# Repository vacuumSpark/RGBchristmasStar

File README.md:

# RGBchristmasStar
Custom PCB for having addressable RGB LEDs driven by an ESP12 (ESP8266) with WLED firmware in a star shaped Christmas ornament normally meant for a tea light

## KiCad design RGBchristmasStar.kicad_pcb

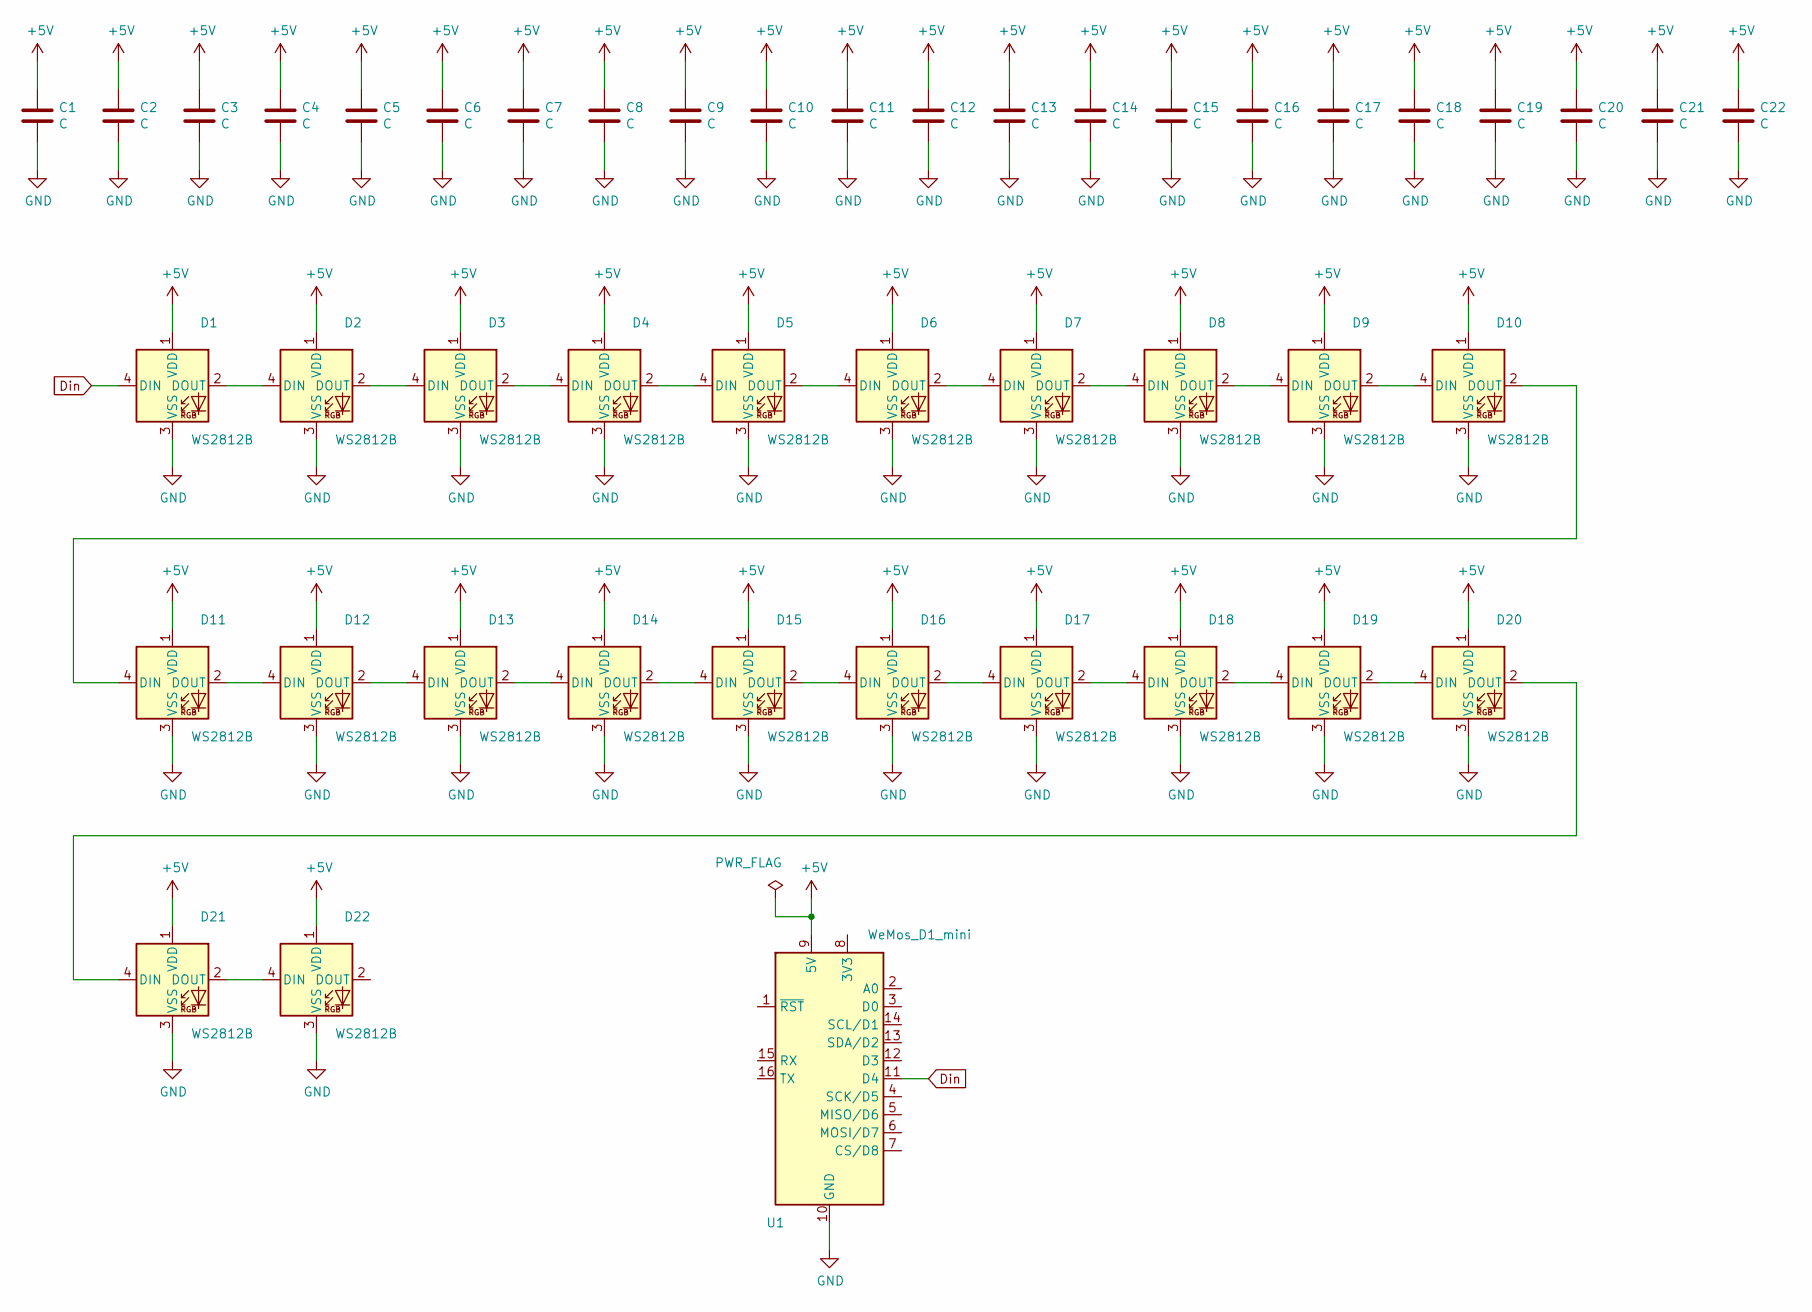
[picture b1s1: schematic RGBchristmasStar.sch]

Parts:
C1, C2, C3, C4, C5, C6, C7, C8, C9, C10, C11, C12, C13, C14, C15, C16, C17, C18, C19, C20, C21, C22: C; C_0805_2012Metric; JLCPCB Part # C28233
D1, D2, D3, D4, D5, D6, D7, D8, D9, D10, D11, D12, D13, D14, D15, D16, D17, D18, D19, D20, D21, D22: WS2812B; WS2812B-Mini; JLCPCB Part # C114583
U1: WeMos_D1_mini; WEMOS_D1_mini_light_SMD_header

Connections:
+5V: C1.1, C2.1, C3.1, C4.1, C5.1, C6.1, C7.1, C8.1, C9.1, C10.1, C11.1, C12.1, C13.1, C14.1, C15.1, C16.1, C17.1, C18.1, C19.1, C20.1, C21.1, C22.1, D1.1 (VDD), D2.1 (VDD), D3.1 (VDD), D4.1 (VDD), D5.1 (VDD), D6.1 (VDD), D7.1 (VDD), D8.1 (VDD), D9.1 (VDD), D10.1 (VDD), D11.1 (VDD), D12.1 (VDD), D13.1 (VDD), D14.1 (VDD), D15.1 (VDD), D16.1 (VDD), D17.1 (VDD), D18.1 (VDD), D19.1 (VDD), D20.1 (VDD), D21.1 (VDD), D22.1 (VDD), U1.9 (5V)
Din: D1.4 (DIN), U1.11 (D4)
GND: C1.2, C2.2, C3.2, C4.2, C5.2, C6.2, C7.2, C8.2, C9.2, C10.2, C11.2, C12.2, C13.2, C14.2, C15.2, C16.2, C17.2, C18.2, C19.2, C20.2, C21.2, C22.2, D1.3 (VSS), D2.3 (VSS), D3.3 (VSS), D4.3 (VSS), D5.3 (VSS), D6.3 (VSS), D7.3 (VSS), D8.3 (VSS), D9.3 (VSS), D10.3 (VSS), D11.3 (VSS), D12.3 (VSS), D13.3 (VSS), D14.3 (VSS), D15.3 (VSS), D16.3 (VSS), D17.3 (VSS), D18.3 (VSS), D19.3 (VSS), D20.3 (VSS), D21.3 (VSS), D22.3 (VSS), U1.10 (GND)
unnamed: D1.2 (DOUT), D2.4 (DIN)
unnamed: D2.2 (DOUT), D3.4 (DIN)
unnamed: D3.2 (DOUT), D4.4 (DIN)
unnamed: D4.2 (DOUT), D5.4 (DIN)
unnamed: D5.2 (DOUT), D6.4 (DIN)
unnamed: D6.2 (DOUT), D7.4 (DIN)
unnamed: D7.2 (DOUT), D8.4 (DIN)
unnamed: D8.2 (DOUT), D9.4 (DIN)
unnamed: D10.2 (DOUT), D11.4 (DIN)
unnamed: D9.2 (DOUT), D10.4 (DIN)
unnamed: D11.2 (DOUT), D12.4 (DIN)
unnamed: D12.2 (DOUT), D13.4 (DIN)
unnamed: D13.2 (DOUT), D14.4 (DIN)
unnamed: D14.2 (DOUT), D15.4 (DIN)
unnamed: D15.2 (DOUT), D16.4 (DIN)
unnamed: D16.2 (DOUT), D17.4 (DIN)
unnamed: D17.2 (DOUT), D18.4 (DIN)
unnamed: D18.2 (DOUT), D19.4 (DIN)
unnamed: D19.2 (DOUT), D20.4 (DIN)
unnamed: D20.2 (DOUT), D21.4 (DIN)
unnamed: D21.2 (DOUT), D22.4 (DIN)

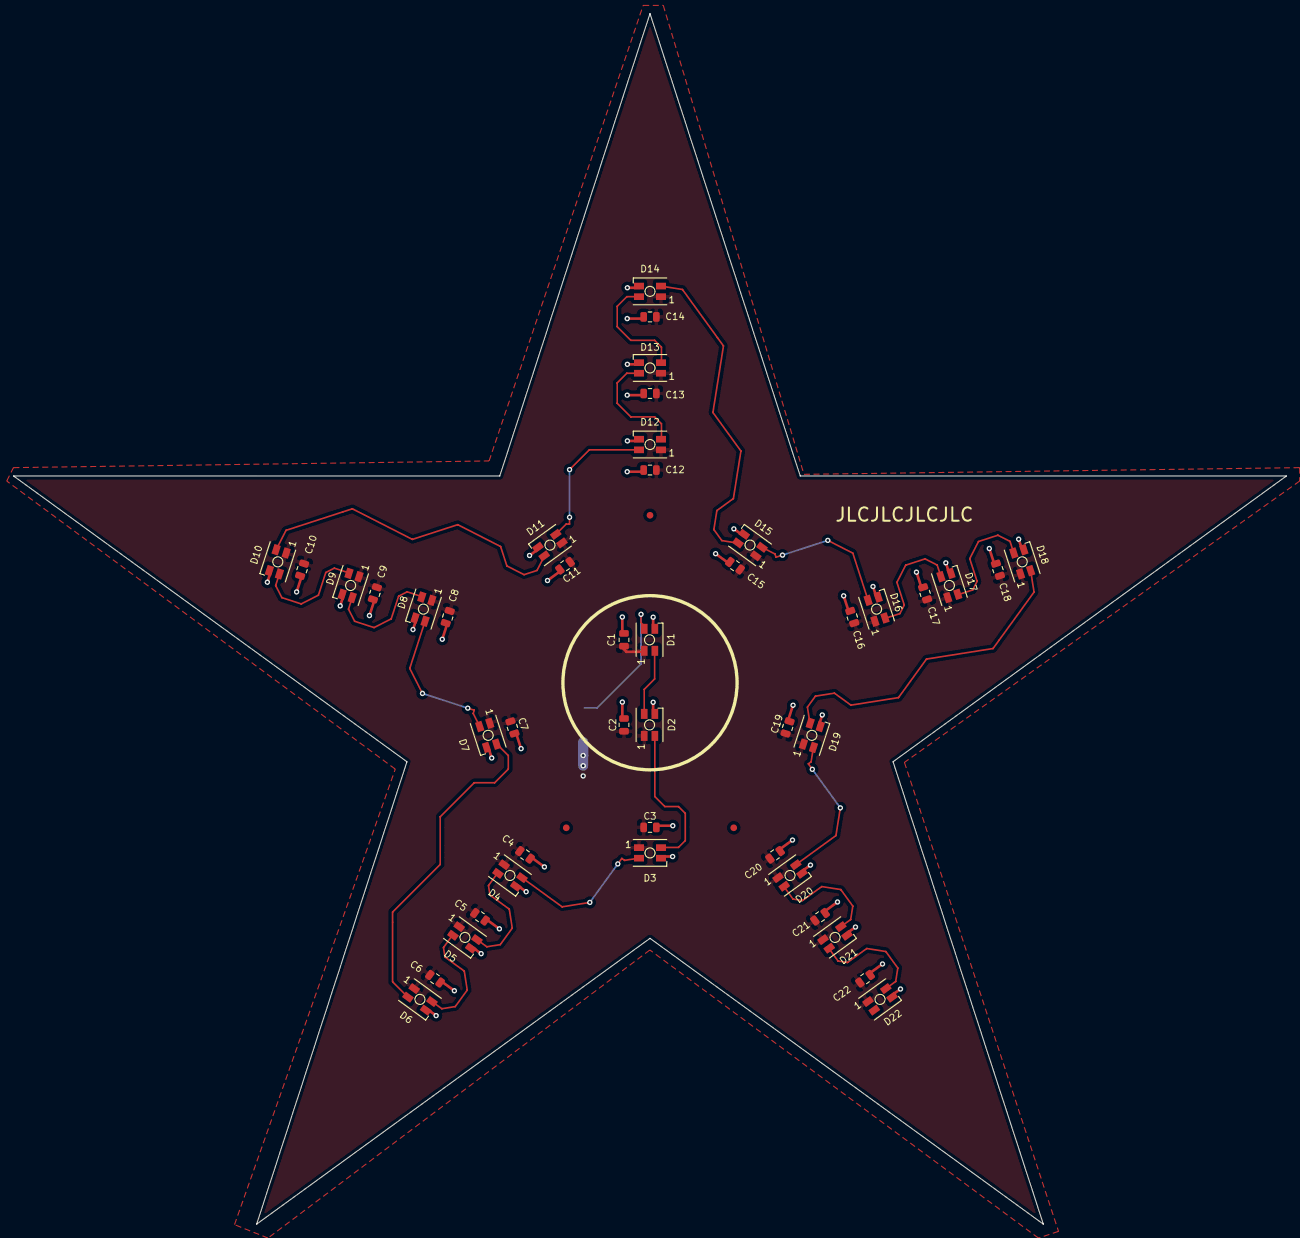
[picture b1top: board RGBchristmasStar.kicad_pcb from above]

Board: 2 copper layers, 190.0 x 180.7 mm, 45 parts (1 on the bottom side), 24 nets.

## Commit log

2021-10-26 created schematic and created board outline
2021-10-30 created new footprints
2021-10-30 Update RGBchristmasStar.kicad_pcb
    Placed LEDs in star with ciruclar array script
2021-10-30 Changed position of components + added routing + pours + fiducials + made silkscreen visible
2021-11-29 first commit to JLCPCB with SMT
